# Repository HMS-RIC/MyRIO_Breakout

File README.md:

# MyRIO_Breakout
Breakout board for NI MyRIO. Brings to BNC connectors 4 analog out, 4 analog in and 14 digital IO. Includes 2 channels of lick detection, 2 solenoid drivers and 3 LED drivers

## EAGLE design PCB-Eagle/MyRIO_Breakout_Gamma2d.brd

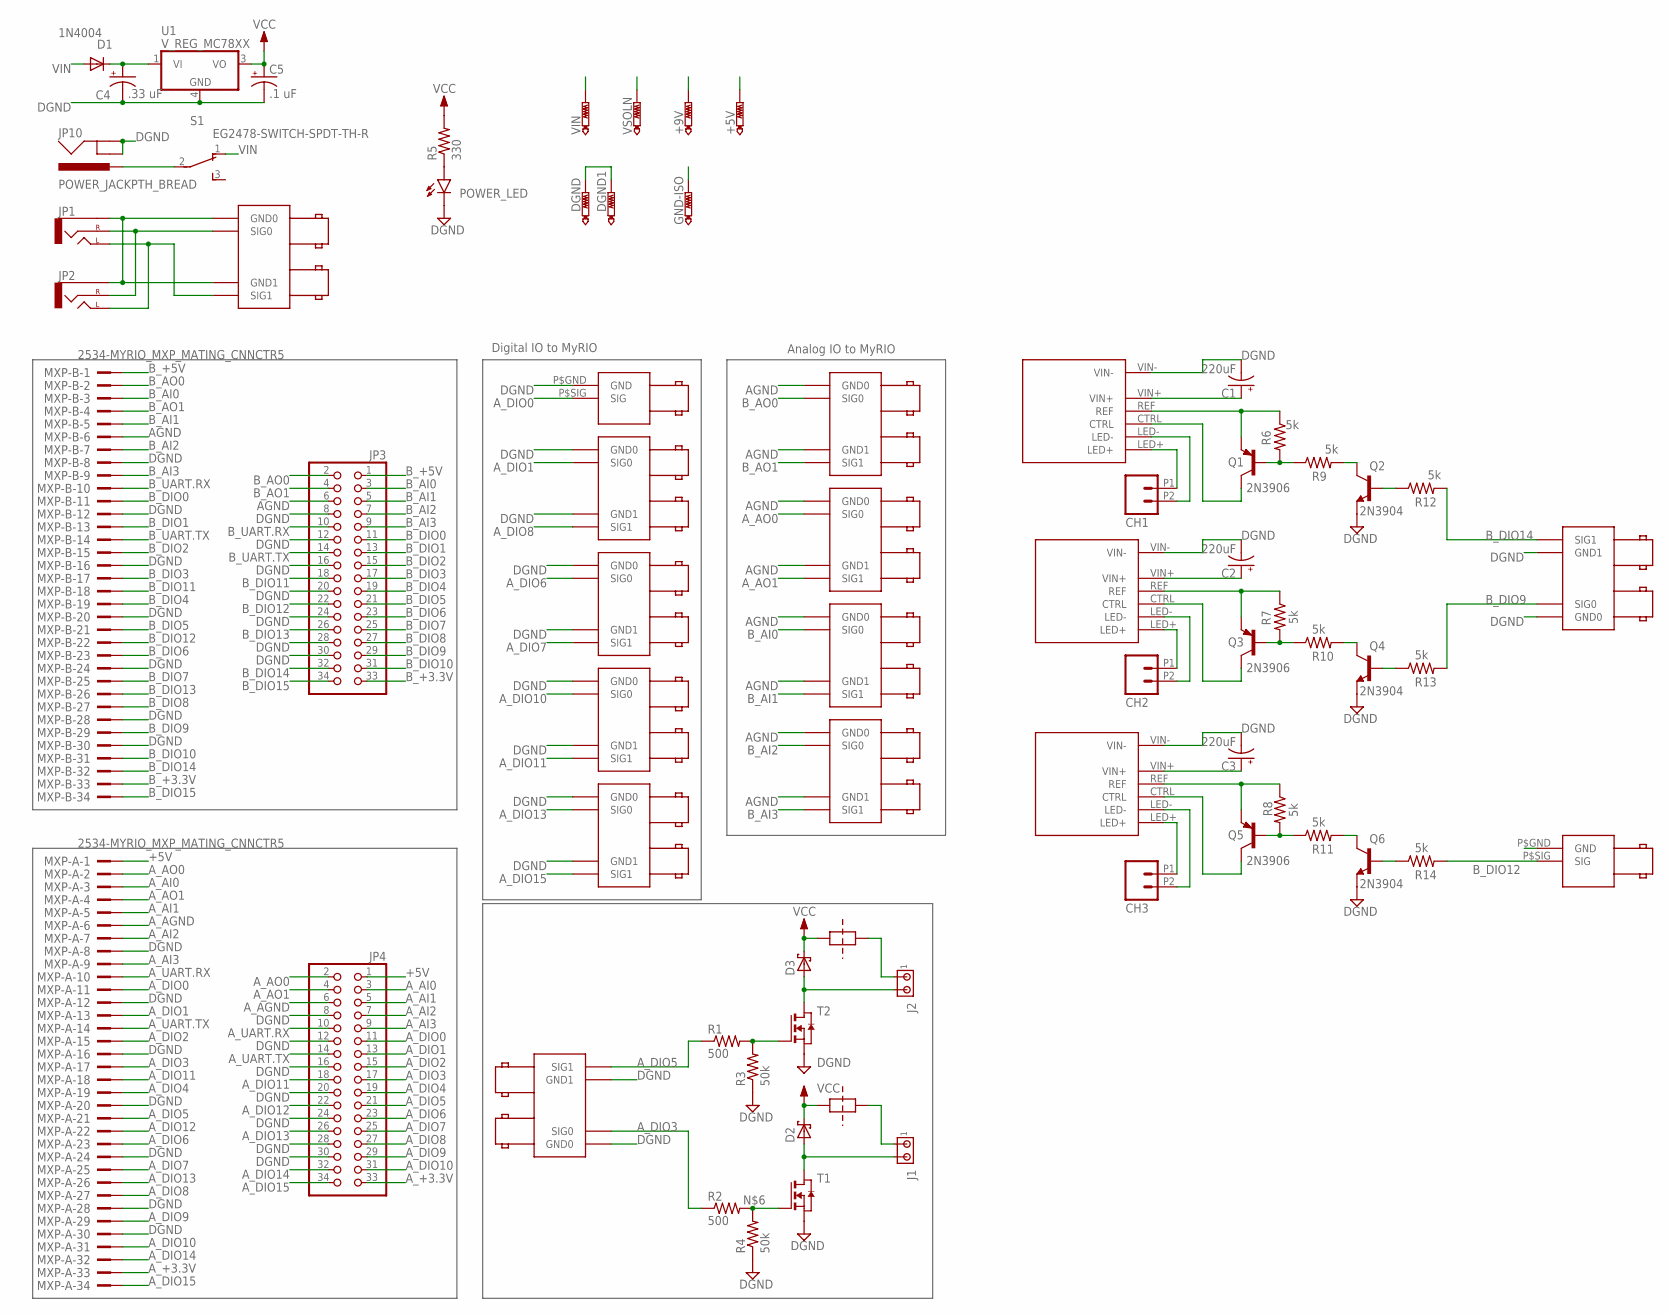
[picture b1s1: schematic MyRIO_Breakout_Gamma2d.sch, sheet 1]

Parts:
+5V, +9V: PTR1PAD1-13Y; P1-13Y
AAO_0,1: BNC_RIGHT_ANGLE_DOUBLE
ACTV_REC: BNC_RIGHT_ANGLE
AUDIO: BNC_RIGHT_ANGLE_DOUBLE
BAI_0,1, BAI_2,3: BNC_RIGHT_ANGLE_DOUBLE
BAO_0,1: BNC_RIGHT_ANGLE_DOUBLE
BUCKPUCK1, BUCKPUCK2, BUCKPUCK3: BUCKPUCK-350-I; BUCKPUCK_I
C1, C2, C3: 220uF; E5-10,5
C4: .33 uF; E2,5-5
C5: .1 uF; E2,5-5
CAMERA: BNC_RIGHT_ANGLE_DOUBLE
CH1, CH2, CH3: M022.54MM_SCREWTERM; 1X02_2.54_SCREWTERM
D1: 1N4004; DO41-10
D2, D3: SCHOTTKY-DIODE; DIODE_SMB
DGND, DGND1: PTR1PAD1-13Y; P1-13Y
D_FREE1_2, D_FREE3_4: BNC_RIGHT_ANGLE_DOUBLE
GND-ISO: PTR1PAD1-13Y; P1-13Y
J1, J2: MTA02-100; 10X02MTA
JP1, JP2: AUDIO-JACKPTH; AUDIO-JACK
JP3, JP4: PINHD-2X17; 2X17
JP5, JP6: CUTABLE_RESISTOR_JUMPER1206; 1206_WITH_TRACE
JP10: POWER_JACKPTH_BREAD; POWER_JACK_PTH_BREAD
LED_CUE_3: BNC_RIGHT_ANGLE
LED_MASK_1,2: BNC_RIGHT_ANGLE_DOUBLE
MXP-A: 2534-MYRIO_MXP_MATING_CNNCTR5; PAK100/2500-5-34-MXP_CONNCTR
MXP-B: 2534-MYRIO_MXP_MATING_CNNCTR5; PAK100/2500-5-34-MXP_CONNCTR
POWER_LED: LED3MM
Q1, Q3, Q5: 2N3906; SOT23-BEC
Q2, Q4, Q6: 2N3904; SOT23-BEC
R1, R2: 500; M1206
R3, R4: 50k; M1206
R5: 330; 0207/10
R6, R7, R8, R9, R10, R11, R12, R13, R14: 5k; 0805S
S1: EG2478-SWITCH-SPDT-TH-R; ESWITCH_500-SSP1M6
SHUTTER: BNC_RIGHT_ANGLE_DOUBLE
SLN: BNC_RIGHT_ANGLE_DOUBLE
T1, T2: NMOSSOT223; SOT223
U1: V_REG_MC78XX; DPAK
VIN: PTR1PAD1-13Y; P1-13Y
VSOLN: PTR1PAD1-13Y; P1-13Y

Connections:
+5V: +5V.TP, JP4.1, MXP-A.1; also elsewhere on the board
+9V: +9V.TP; also elsewhere on the board
AGND: AAO_0,1.P$GND0 (GND0), AAO_0,1.P$GND1 (GND1), BAI_0,1.P$GND0 (GND0), BAI_0,1.P$GND1 (GND1), BAI_2,3.P$GND0 (GND0), BAI_2,3.P$GND1 (GND1), BAO_0,1.P$GND0 (GND0), BAO_0,1.P$GND1 (GND1), JP3.6, MXP-B.6; also elsewhere on the board
A_+3.3V: JP4.33, MXP-A.33
A_AGND: JP4.6, MXP-A.6
A_AI0: JP4.3, MXP-A.3
A_AI1: JP4.5, MXP-A.5
A_AI2: JP4.7, MXP-A.7
A_AI3: JP4.9, MXP-A.9
A_AO0: AAO_0,1.P$SIG0 (SIG0), JP4.2, MXP-A.2
A_AO1: AAO_0,1.P$SIG1 (SIG1), JP4.4, MXP-A.4
A_DIO0: ACTV_REC.P$SIG (SIG), JP4.11, MXP-A.11
A_DIO1: CAMERA.P$SIG0 (SIG0), JP4.13, MXP-A.13
A_DIO2: JP4.15, MXP-A.15; also elsewhere on the board
A_DIO3: JP4.17, MXP-A.17, R2.1, SLN.P$SIG0 (SIG0)
A_DIO4: JP4.19, MXP-A.19; also elsewhere on the board
A_DIO5: JP4.21, MXP-A.21, R1.1, SLN.P$SIG1 (SIG1)
A_DIO6: JP4.23, MXP-A.23, SHUTTER.P$SIG0 (SIG0)
A_DIO7: JP4.25, MXP-A.25, SHUTTER.P$SIG1 (SIG1)
A_DIO8: CAMERA.P$SIG1 (SIG1), JP4.27, MXP-A.27
A_DIO9: JP4.29, MXP-A.29
A_DIO10: D_FREE1_2.P$SIG0 (SIG0), JP4.31, MXP-A.31
A_DIO11: D_FREE1_2.P$SIG1 (SIG1), JP4.18, MXP-A.18
A_DIO12: JP4.22, MXP-A.22
A_DIO13: D_FREE3_4.P$SIG0 (SIG0), JP4.26, MXP-A.26
A_DIO14: JP4.32, MXP-A.32
A_DIO15: D_FREE3_4.P$SIG1 (SIG1), JP4.34, MXP-A.34
A_UART.RX: JP4.10, MXP-A.10
A_UART.TX: JP4.14, MXP-A.14
BCKPCK_CTRL2: Q4.C, R10.2
BCKPCK_CTRL3: Q6.C, R11.2
B_+3.3V: JP3.33, MXP-B.33
B_+5V: JP3.1, MXP-B.1
B_AI0: BAI_0,1.P$SIG0 (SIG0), JP3.3, MXP-B.3
B_AI1: BAI_0,1.P$SIG1 (SIG1), JP3.5, MXP-B.5
B_AI2: BAI_2,3.P$SIG0 (SIG0), JP3.7, MXP-B.7
B_AI3: BAI_2,3.P$SIG1 (SIG1), JP3.9, MXP-B.9
B_AO0: BAO_0,1.P$SIG0 (SIG0), JP3.2, MXP-B.2
B_AO1: BAO_0,1.P$SIG1 (SIG1), JP3.4, MXP-B.4
B_DIO0: JP3.11, MXP-B.11
B_DIO1: JP3.13, MXP-B.13
B_DIO2: JP3.15, MXP-B.15
B_DIO3: JP3.17, MXP-B.17
B_DIO4: JP3.19, MXP-B.19
B_DIO5: JP3.21, MXP-B.21
B_DIO6: JP3.23, MXP-B.23
B_DIO7: JP3.25, MXP-B.25
B_DIO8: JP3.27, MXP-B.27
B_DIO9: JP3.29, LED_MASK_1,2.P$SIG0 (SIG0), MXP-B.29, R13.2
B_DIO10: JP3.31, MXP-B.31
B_DIO11: JP3.18, MXP-B.18
B_DIO12: JP3.22, LED_CUE_3.P$SIG (SIG), MXP-B.22, R14.2
B_DIO13: JP3.26, MXP-B.26
B_DIO14: JP3.32, LED_MASK_1,2.P$SIG1 (SIG1), MXP-B.32, R12.2
B_DIO15: JP3.34, MXP-B.34
B_UART.RX: JP3.10, MXP-B.10
B_UART.TX: JP3.14, MXP-B.14
CTRL1: BUCKPUCK1.CTRL, Q1.C
CTRL2: BUCKPUCK2.CTRL, Q3.C
CTRL3: BUCKPUCK3.CTRL, Q5.C
DGND: ACTV_REC.P$GND (GND), BUCKPUCK1.LED-, BUCKPUCK1.VIN-, BUCKPUCK2.LED-, BUCKPUCK2.VIN-, BUCKPUCK3.LED-, BUCKPUCK3.VIN-, C1.-, C2.-, C3.-, C4.-, C5.-, CAMERA.P$GND0 (GND0), CAMERA.P$GND1 (GND1), CH1.P2 (2), CH2.P2 (2), CH3.P2 (2), DGND.TP, DGND1.TP, D_FREE1_2.P$GND0 (GND0), D_FREE1_2.P$GND1 (GND1), D_FREE3_4.P$GND0 (GND0), D_FREE3_4.P$GND1 (GND1), JP3.8, JP3.12, JP3.16, JP3.20, JP3.24, JP3.28, JP3.30, JP4.8, JP4.12, JP4.16, JP4.20, JP4.24, JP4.28, JP4.30, JP10.GND, JP10.GNDBREAK, LED_CUE_3.P$GND (GND), LED_MASK_1,2.P$GND0 (GND0), LED_MASK_1,2.P$GND1 (GND1), MXP-A.8, MXP-A.12, MXP-A.16, MXP-A.20, MXP-A.24, MXP-A.28, MXP-A.30, MXP-B.8, MXP-B.12, MXP-B.16, MXP-B.20, MXP-B.24, MXP-B.28, MXP-B.30, POWER_LED.K (C), Q2.E, Q4.E, Q6.E, R3.1, R4.1, SHUTTER.P$GND0 (GND0), SHUTTER.P$GND1 (GND1), SLN.P$GND0 (GND0), SLN.P$GND1 (GND1), T1.3 (S), T2.3 (S), U1.4 (GND); also elsewhere on the board
GND-ISO: GND-ISO.TP; also elsewhere on the board
LED1+: BUCKPUCK1.LED+, CH1.P1 (1)
LED2+: BUCKPUCK2.LED+, CH2.P1 (1)
LED3+: BUCKPUCK3.LED+, CH3.P1 (1)
unnamed: R1.2, R3.2, T2.1 (G)
unnamed: AUDIO.P$GND0 (GND0), AUDIO.P$GND1 (GND1), JP1.SLEEVE, JP2.SLEEVE
unnamed: AUDIO.P$SIG0 (SIG0), JP1.RING (RIGHT), JP2.RING (RIGHT)
unnamed: AUDIO.P$SIG1 (SIG1), JP1.TIP (LEFT), JP2.TIP (LEFT)
unnamed: R2.2, R4.2, T1.1 (G)
unnamed: BUCKPUCK3.REF, Q5.E, R8.1
unnamed: POWER_LED.A, R5.1
unnamed: Q5.B, R8.2, R11.1
unnamed: BUCKPUCK1.VIN+, BUCKPUCK2.VIN+, BUCKPUCK3.VIN+, C1.+, C2.+, C3.+, C4.+, D1.C, U1.1 (VI), VIN.TP
unnamed: BUCKPUCK1.REF, Q1.E, R6.1
unnamed: BUCKPUCK2.REF, Q3.E, R7.1
unnamed: Q6.B, R14.1
unnamed: Q4.B, R13.1
unnamed: Q1.B, R6.2, R9.1
unnamed: Q2.B, R12.1
unnamed: J1.1, JP6.2
unnamed: Q3.B, R7.2, R10.1
unnamed: JP10.PWR, S1.2
unnamed: J2.1, JP5.2
unnamed: Q2.C, R9.2
VCC: C5.+, D2.C (A), D3.C (A), JP5.1, JP6.1, R5.2, U1.3 (VO), VSOLN.TP
VIN: D1.A, S1.1
VOUT-1: D2.A (C), J1.2, T1.2 (D), T1.4 (D)
VOUT-2: D3.A (C), J2.2, T2.2 (D), T2.4 (D)

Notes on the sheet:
Digital IO to MyRIO
Analog IO to MyRIO

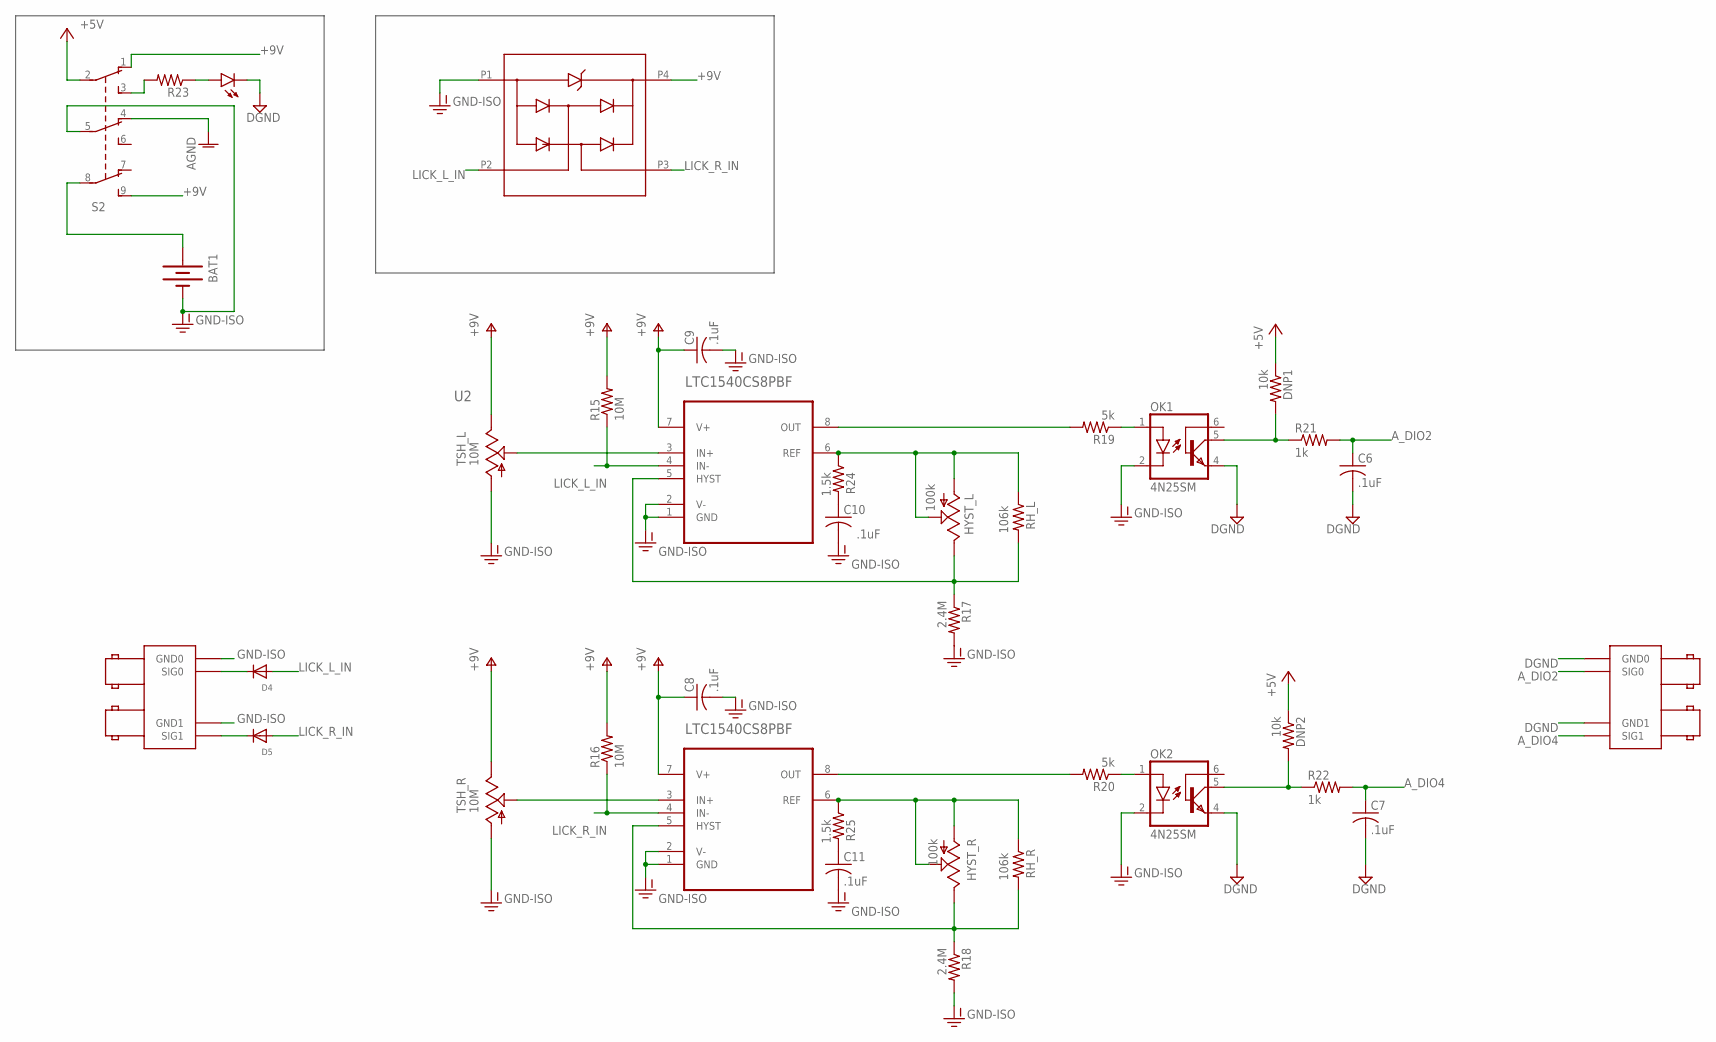
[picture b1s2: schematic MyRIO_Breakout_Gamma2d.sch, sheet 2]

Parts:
BAT1: BATTERY9V; BATTCON_9V
C6, C7, C8, C9, C10, C11: .1uF; C0805
D4, D5: DIODE_SOD-123FL; SOD-123FL
DNP1, DNP2: 10k; M0805
HYST_L: 100k; B25P
HYST_R: 100k; B25P
ISOLATED: LED3MM
LICK: BNC_RIGHT_ANGLE_DOUBLE
LICK_INPUTS: BNC_RIGHT_ANGLE_DOUBLE
OK1, OK2: 4N25SM; DIL6-SMD
R15, R16: 10M; M0805
R17, R18: 2.4M; M0805
R19, R20: 5k; M0805
R21, R22: 1k; M0805
R23: 330; 0207/10
R24, R25: 1.5k; M0805
RH_L: 106k; M0805
RH_R: 106k; M0805
S2: SWITCH-3PDT-TH-V; NKK-M20-9PIN-VERTICAL
TSH_L: 10M; B25P
TSH_R: 10M; B25P
U2, U3: LTC1540CS8PBF; SOIC127P600X175-8N
U$1: CD143A-12_TVS; SOT-143

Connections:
+5V: DNP1.1, DNP2.1, S2.2 (P1); also elsewhere on the board
+9V: C8.1, C9.1, R15.2, R16.2, S2.1 (O1), S2.9 (S3), TSH_L.E, TSH_R.E, U2.7 (V+), U3.7 (V+), U$1.P4; also elsewhere on the board
AGND: S2.4 (O2); also elsewhere on the board
A_DIO2: C6.1, LICK.P$SIG0 (SIG0), R21.2; also elsewhere on the board
A_DIO4: C7.1, LICK.P$SIG1 (SIG1), R22.2; also elsewhere on the board
DGND: C6.2, C7.2, ISOLATED.K (C), LICK.P$GND0 (GND0), LICK.P$GND1 (GND1), OK1.4 (EMI), OK2.4 (EMI); also elsewhere on the board
GND-ISO: BAT1.-, C8.2, C9.2, C10.2, C11.2, LICK_INPUTS.P$GND0 (GND0), LICK_INPUTS.P$GND1 (GND1), OK1.2 (C), OK2.2 (C), R17.2, R18.2, S2.5 (P2), TSH_L.A, TSH_R.A, U2.1 (GND), U2.2 (V-), U3.1 (GND), U3.2 (V-), U$1.P1; also elsewhere on the board
LICK_L_IN: D4.A, R15.1, U2.4 (IN-), U$1.P2
LICK_R_IN: D5.A, R16.1, U3.4 (IN-), U$1.P3
unnamed: D4.C, LICK_INPUTS.P$SIG0 (SIG0)
unnamed: C10.1, R24.2
unnamed: D5.C, LICK_INPUTS.P$SIG1 (SIG1)
unnamed: C11.1, R25.2
unnamed: BAT1.+, S2.8 (P3)
unnamed: ISOLATED.A, R23.1
unnamed: TSH_R.S, U3.3 (IN+)
unnamed: R23.2, S2.3 (S1)
unnamed: OK1.1 (A), R19.1
unnamed: R19.2, U2.8 (OUT)
unnamed: DNP1.2, OK1.5 (COL), R21.1
unnamed: HYST_L.A, HYST_L.S, R24.1, RH_L.1, U2.6 (REF)
unnamed: HYST_L.E, R17.1, RH_L.2, U2.5 (HYST)
unnamed: OK2.1 (A), R20.1
unnamed: R20.2, U3.8 (OUT)
unnamed: TSH_L.S, U2.3 (IN+)
unnamed: DNP2.2, OK2.5 (COL), R22.1
unnamed: HYST_R.A, HYST_R.S, R25.1, RH_R.1, U3.6 (REF)
unnamed: HYST_R.E, R18.1, RH_R.2, U3.5 (HYST)

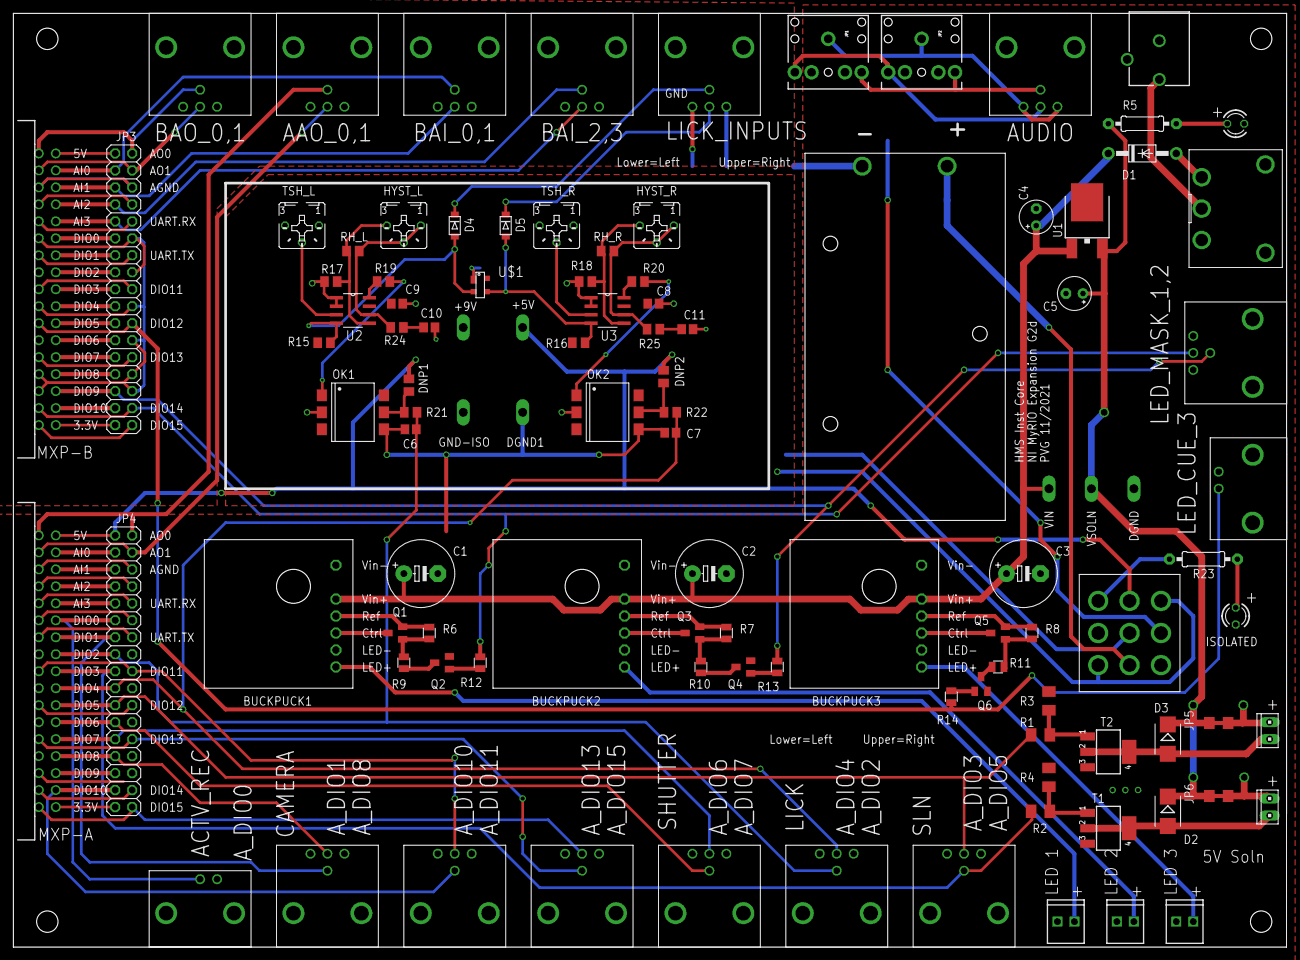
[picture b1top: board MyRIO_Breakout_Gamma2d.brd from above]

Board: 2 copper layers, 190.5 x 139.7 mm, 107 parts (0 on the bottom side), 110 nets.

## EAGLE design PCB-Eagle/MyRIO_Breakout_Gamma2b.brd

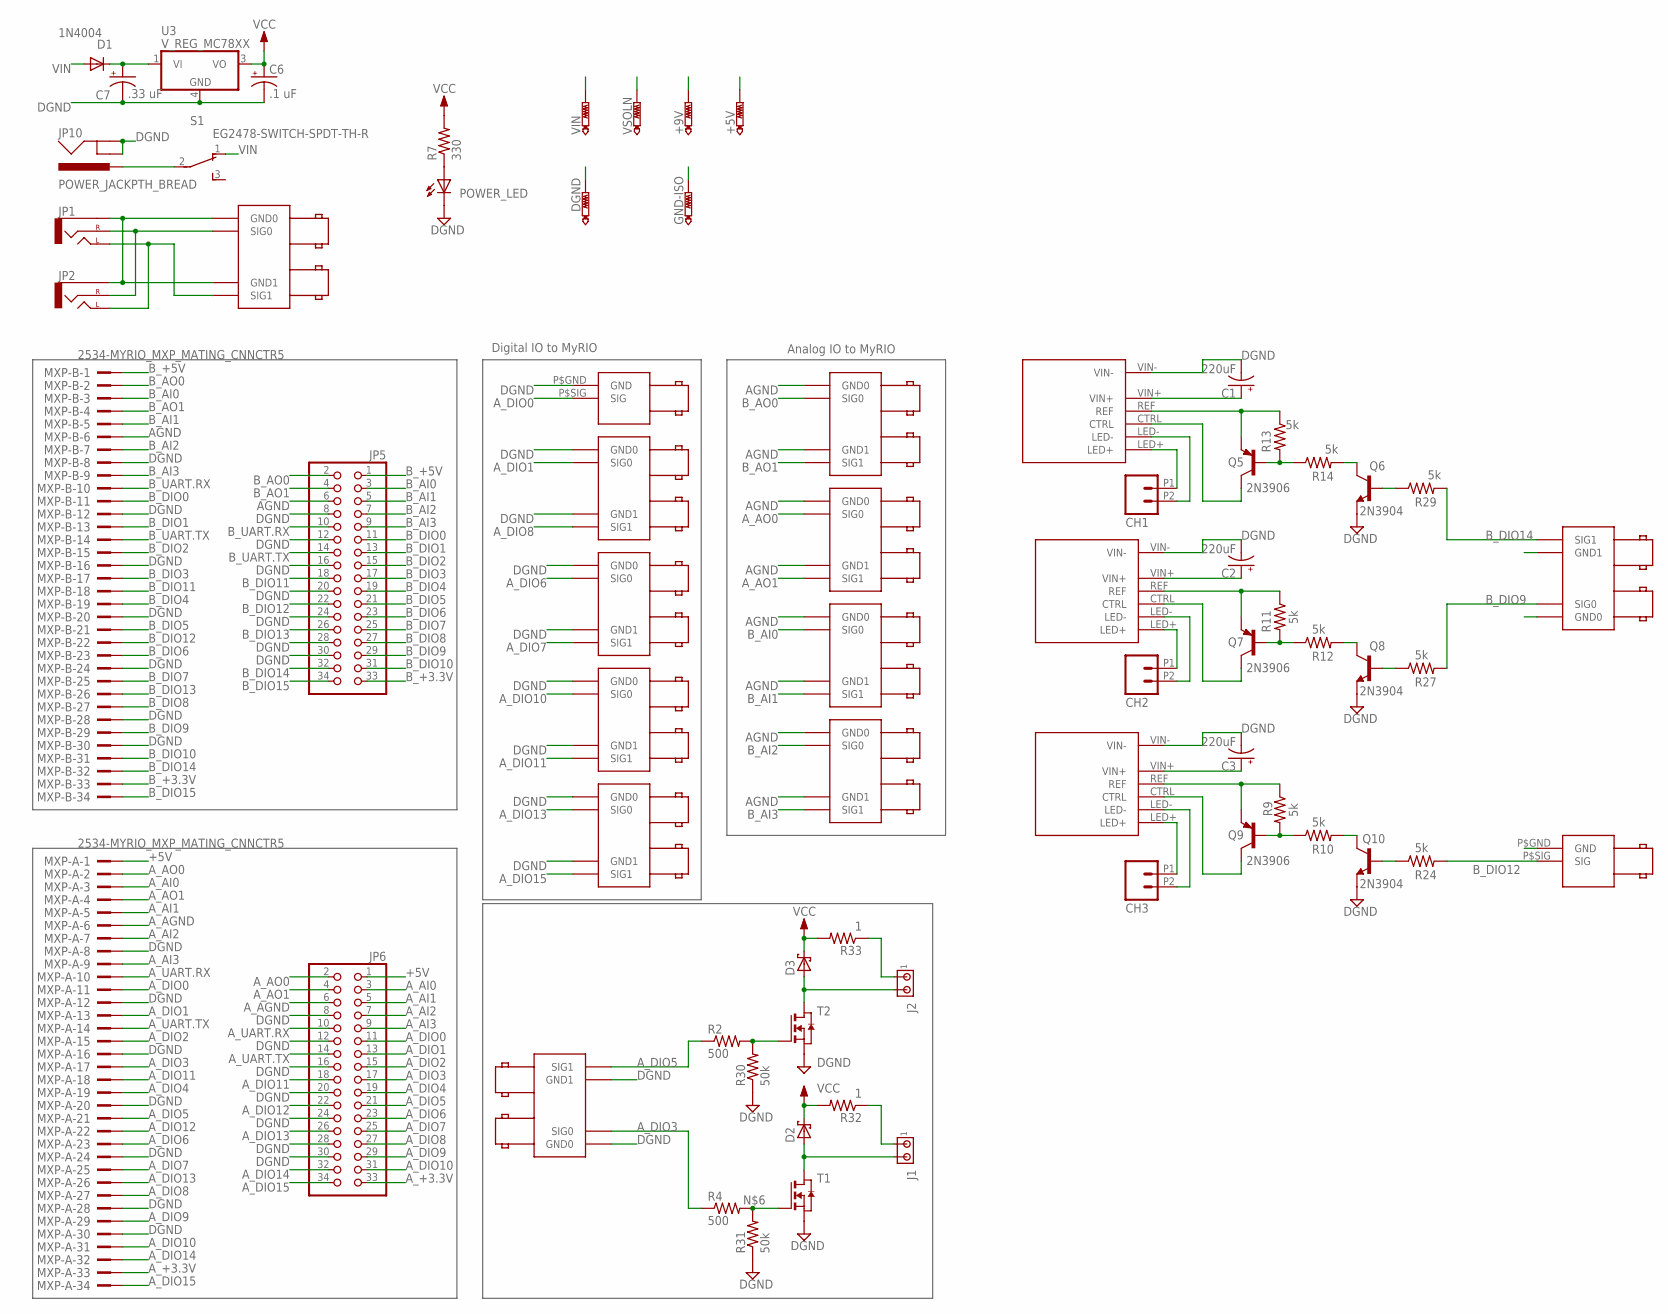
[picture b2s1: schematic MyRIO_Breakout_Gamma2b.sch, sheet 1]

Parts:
+5V, +9V: PTR1PAD1-17Y; P1-17Y
AAO_0,1: BNC_RIGHT_ANGLE_DOUBLE
ACTV_REC: BNC_RIGHT_ANGLE
AUDIO: BNC_RIGHT_ANGLE_DOUBLE
BAI_0,1, BAI_2,3: BNC_RIGHT_ANGLE_DOUBLE
BAO_0,1: BNC_RIGHT_ANGLE_DOUBLE
BUCKPUCK1, BUCKPUCK2, BUCKPUCK3: BUCKPUCK-350-I; BUCKPUCK_I
C1, C2, C3: 220uF; E5-10,5
C6: .1 uF; E2,5-5
C7: .33 uF; E2,5-5
CAMERA: BNC_RIGHT_ANGLE_DOUBLE
CH1, CH2, CH3: M022.54MM_SCREWTERM; 1X02_2.54_SCREWTERM
D1: 1N4004; DO41-10
D2, D3: SCHOTTKY-DIODE; DIODE_SMB
DGND: PTR1PAD1-17Y; P1-17Y
D_FREE1_2, D_FREE3_4: BNC_RIGHT_ANGLE_DOUBLE
GND-ISO: PTR1PAD1-17Y; P1-17Y
J1, J2: MTA02-100; 10X02MTA
JP1, JP2: AUDIO-JACKPTH; AUDIO-JACK
JP5, JP6: PINHD-2X17; 2X17
JP10: POWER_JACKPTH_BREAD; POWER_JACK_PTH_BREAD
LED_CUE: BNC_RIGHT_ANGLE
LED_MASK: BNC_RIGHT_ANGLE_DOUBLE
MXP-A: 2534-MYRIO_MXP_MATING_CNNCTR5; PAK100/2500-5-34-MXP_CONNCTR
MXP-B: 2534-MYRIO_MXP_MATING_CNNCTR5; PAK100/2500-5-34-MXP_CONNCTR
POWER_LED: LED3MM
Q5, Q7, Q9: 2N3906; SOT23-BEC
Q6, Q8, Q10: 2N3904; SOT23-BEC
R2, R4: 500; M1206
R7: 330; 0207/10
R9, R10, R11, R12, R13, R14, R24, R27, R29: 5k; 0805S
R30, R31: 50k; M1206
R32, R33: 1; M1206
S1: EG2478-SWITCH-SPDT-TH-R; ESWITCH_500-SSP1M6
SHUTTER: BNC_RIGHT_ANGLE_DOUBLE
SLN: BNC_RIGHT_ANGLE_DOUBLE
T1, T2: NMOSSOT223; SOT223
U3: V_REG_MC78XX; DPAK
VIN: PTR1PAD1-17Y; P1-17Y
VSOLN: PTR1PAD1-17Y; P1-17Y

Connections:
+5V: +5V.TP, JP6.1, MXP-A.1; also elsewhere on the board
+9V: +9V.TP; also elsewhere on the board
AGND: AAO_0,1.P$GND0 (GND0), AAO_0,1.P$GND1 (GND1), BAI_0,1.P$GND0 (GND0), BAI_0,1.P$GND1 (GND1), BAI_2,3.P$GND0 (GND0), BAI_2,3.P$GND1 (GND1), BAO_0,1.P$GND0 (GND0), BAO_0,1.P$GND1 (GND1), JP5.6, MXP-B.6; also elsewhere on the board
A_+3.3V: JP6.33, MXP-A.33
A_AGND: JP6.6, MXP-A.6
A_AI0: JP6.3, MXP-A.3
A_AI1: JP6.5, MXP-A.5
A_AI2: JP6.7, MXP-A.7
A_AI3: JP6.9, MXP-A.9
A_AO0: AAO_0,1.P$SIG0 (SIG0), JP6.2, MXP-A.2
A_AO1: AAO_0,1.P$SIG1 (SIG1), JP6.4, MXP-A.4
A_DIO0: ACTV_REC.P$SIG (SIG), JP6.11, MXP-A.11
A_DIO1: CAMERA.P$SIG0 (SIG0), JP6.13, MXP-A.13
A_DIO2: JP6.15, MXP-A.15; also elsewhere on the board
A_DIO3: JP6.17, MXP-A.17, R4.1, SLN.P$SIG0 (SIG0)
A_DIO4: JP6.19, MXP-A.19; also elsewhere on the board
A_DIO5: JP6.21, MXP-A.21, R2.1, SLN.P$SIG1 (SIG1)
A_DIO6: JP6.23, MXP-A.23, SHUTTER.P$SIG0 (SIG0)
A_DIO7: JP6.25, MXP-A.25, SHUTTER.P$SIG1 (SIG1)
A_DIO8: CAMERA.P$SIG1 (SIG1), JP6.27, MXP-A.27
A_DIO9: JP6.29, MXP-A.29
A_DIO10: D_FREE1_2.P$SIG0 (SIG0), JP6.31, MXP-A.31
A_DIO11: D_FREE1_2.P$SIG1 (SIG1), JP6.18, MXP-A.18
A_DIO12: JP6.22, MXP-A.22
A_DIO13: D_FREE3_4.P$SIG0 (SIG0), JP6.26, MXP-A.26
A_DIO14: JP6.32, MXP-A.32
A_DIO15: D_FREE3_4.P$SIG1 (SIG1), JP6.34, MXP-A.34
A_UART.RX: JP6.10, MXP-A.10
A_UART.TX: JP6.14, MXP-A.14
BCKPCK_CTRL2: Q8.C, R12.2
BCKPCK_CTRL3: Q10.C, R10.2
B_+3.3V: JP5.33, MXP-B.33
B_+5V: JP5.1, MXP-B.1
B_AI0: BAI_0,1.P$SIG0 (SIG0), JP5.3, MXP-B.3
B_AI1: BAI_0,1.P$SIG1 (SIG1), JP5.5, MXP-B.5
B_AI2: BAI_2,3.P$SIG0 (SIG0), JP5.7, MXP-B.7
B_AI3: BAI_2,3.P$SIG1 (SIG1), JP5.9, MXP-B.9
B_AO0: BAO_0,1.P$SIG0 (SIG0), JP5.2, MXP-B.2
B_AO1: BAO_0,1.P$SIG1 (SIG1), JP5.4, MXP-B.4
B_DIO0: JP5.11, MXP-B.11
B_DIO1: JP5.13, MXP-B.13
B_DIO2: JP5.15, MXP-B.15
B_DIO3: JP5.17, MXP-B.17
B_DIO4: JP5.19, MXP-B.19
B_DIO5: JP5.21, MXP-B.21
B_DIO6: JP5.23, MXP-B.23
B_DIO7: JP5.25, MXP-B.25
B_DIO8: JP5.27, MXP-B.27
B_DIO9: JP5.29, LED_MASK.P$SIG0 (SIG0), MXP-B.29, R27.2
B_DIO10: JP5.31, MXP-B.31
B_DIO11: JP5.18, MXP-B.18
B_DIO12: JP5.22, LED_CUE.P$SIG (SIG), MXP-B.22, R24.2
B_DIO13: JP5.26, MXP-B.26
B_DIO14: JP5.32, LED_MASK.P$SIG1 (SIG1), MXP-B.32, R29.2
B_DIO15: JP5.34, MXP-B.34
B_UART.RX: JP5.10, MXP-B.10
B_UART.TX: JP5.14, MXP-B.14
CTRL1: BUCKPUCK1.CTRL, Q5.C
CTRL2: BUCKPUCK2.CTRL, Q7.C
CTRL3: BUCKPUCK3.CTRL, Q9.C
DGND: ACTV_REC.P$GND (GND), BUCKPUCK1.LED-, BUCKPUCK1.VIN-, BUCKPUCK2.LED-, BUCKPUCK2.VIN-, BUCKPUCK3.LED-, BUCKPUCK3.VIN-, C1.-, C2.-, C3.-, C6.-, C7.-, CAMERA.P$GND0 (GND0), CAMERA.P$GND1 (GND1), CH1.P2 (2), CH2.P2 (2), CH3.P2 (2), DGND.TP, D_FREE1_2.P$GND0 (GND0), D_FREE1_2.P$GND1 (GND1), D_FREE3_4.P$GND0 (GND0), D_FREE3_4.P$GND1 (GND1), JP5.8, JP5.12, JP5.16, JP5.20, JP5.24, JP5.28, JP5.30, JP6.8, JP6.12, JP6.16, JP6.20, JP6.24, JP6.28, JP6.30, JP10.GND, JP10.GNDBREAK, LED_CUE.P$GND (GND), LED_MASK.P$GND0 (GND0), LED_MASK.P$GND1 (GND1), MXP-A.8, MXP-A.12, MXP-A.16, MXP-A.20, MXP-A.24, MXP-A.28, MXP-A.30, MXP-B.8, MXP-B.12, MXP-B.16, MXP-B.20, MXP-B.24, MXP-B.28, MXP-B.30, POWER_LED.K (C), Q6.E, Q8.E, Q10.E, R30.1, R31.1, SHUTTER.P$GND0 (GND0), SHUTTER.P$GND1 (GND1), SLN.P$GND0 (GND0), SLN.P$GND1 (GND1), T1.3 (S), T2.3 (S), U3.4 (GND); also elsewhere on the board
GND-ISO: GND-ISO.TP; also elsewhere on the board
LED1+: BUCKPUCK1.LED+, CH1.P1 (1)
LED2+: BUCKPUCK2.LED+, CH2.P1 (1)
LED3+: BUCKPUCK3.LED+, CH3.P1 (1)
unnamed: R2.2, R30.2, T2.1 (G)
unnamed: AUDIO.P$GND0 (GND0), AUDIO.P$GND1 (GND1), JP1.SLEEVE, JP2.SLEEVE
unnamed: AUDIO.P$SIG0 (SIG0), JP1.RING (RIGHT), JP2.RING (RIGHT)
unnamed: AUDIO.P$SIG1 (SIG1), JP1.TIP (LEFT), JP2.TIP (LEFT)
unnamed: R4.2, R31.2, T1.1 (G)
unnamed: BUCKPUCK3.REF, Q9.E, R9.1
unnamed: POWER_LED.A, R7.1
unnamed: Q9.B, R9.2, R10.1
unnamed: BUCKPUCK1.VIN+, BUCKPUCK2.VIN+, BUCKPUCK3.VIN+, C1.+, C2.+, C3.+, C7.+, D1.C, U3.1 (VI), VIN.TP
unnamed: BUCKPUCK1.REF, Q5.E, R13.1
unnamed: BUCKPUCK2.REF, Q7.E, R11.1
unnamed: Q10.B, R24.1
unnamed: Q8.B, R27.1
unnamed: Q5.B, R13.2, R14.1
unnamed: Q6.B, R29.1
unnamed: J1.1, R32.1
unnamed: Q7.B, R11.2, R12.1
unnamed: JP10.PWR, S1.2
unnamed: J2.1, R33.1
unnamed: Q6.C, R14.2
VCC: C6.+, D2.C (A), D3.C (A), R7.2, R32.2, R33.2, U3.3 (VO), VSOLN.TP
VIN: D1.A, S1.1
VOUT-1: D2.A (C), J1.2, T1.2 (D), T1.4 (D)
VOUT-2: D3.A (C), J2.2, T2.2 (D), T2.4 (D)

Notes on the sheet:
Digital IO to MyRIO
Analog IO to MyRIO

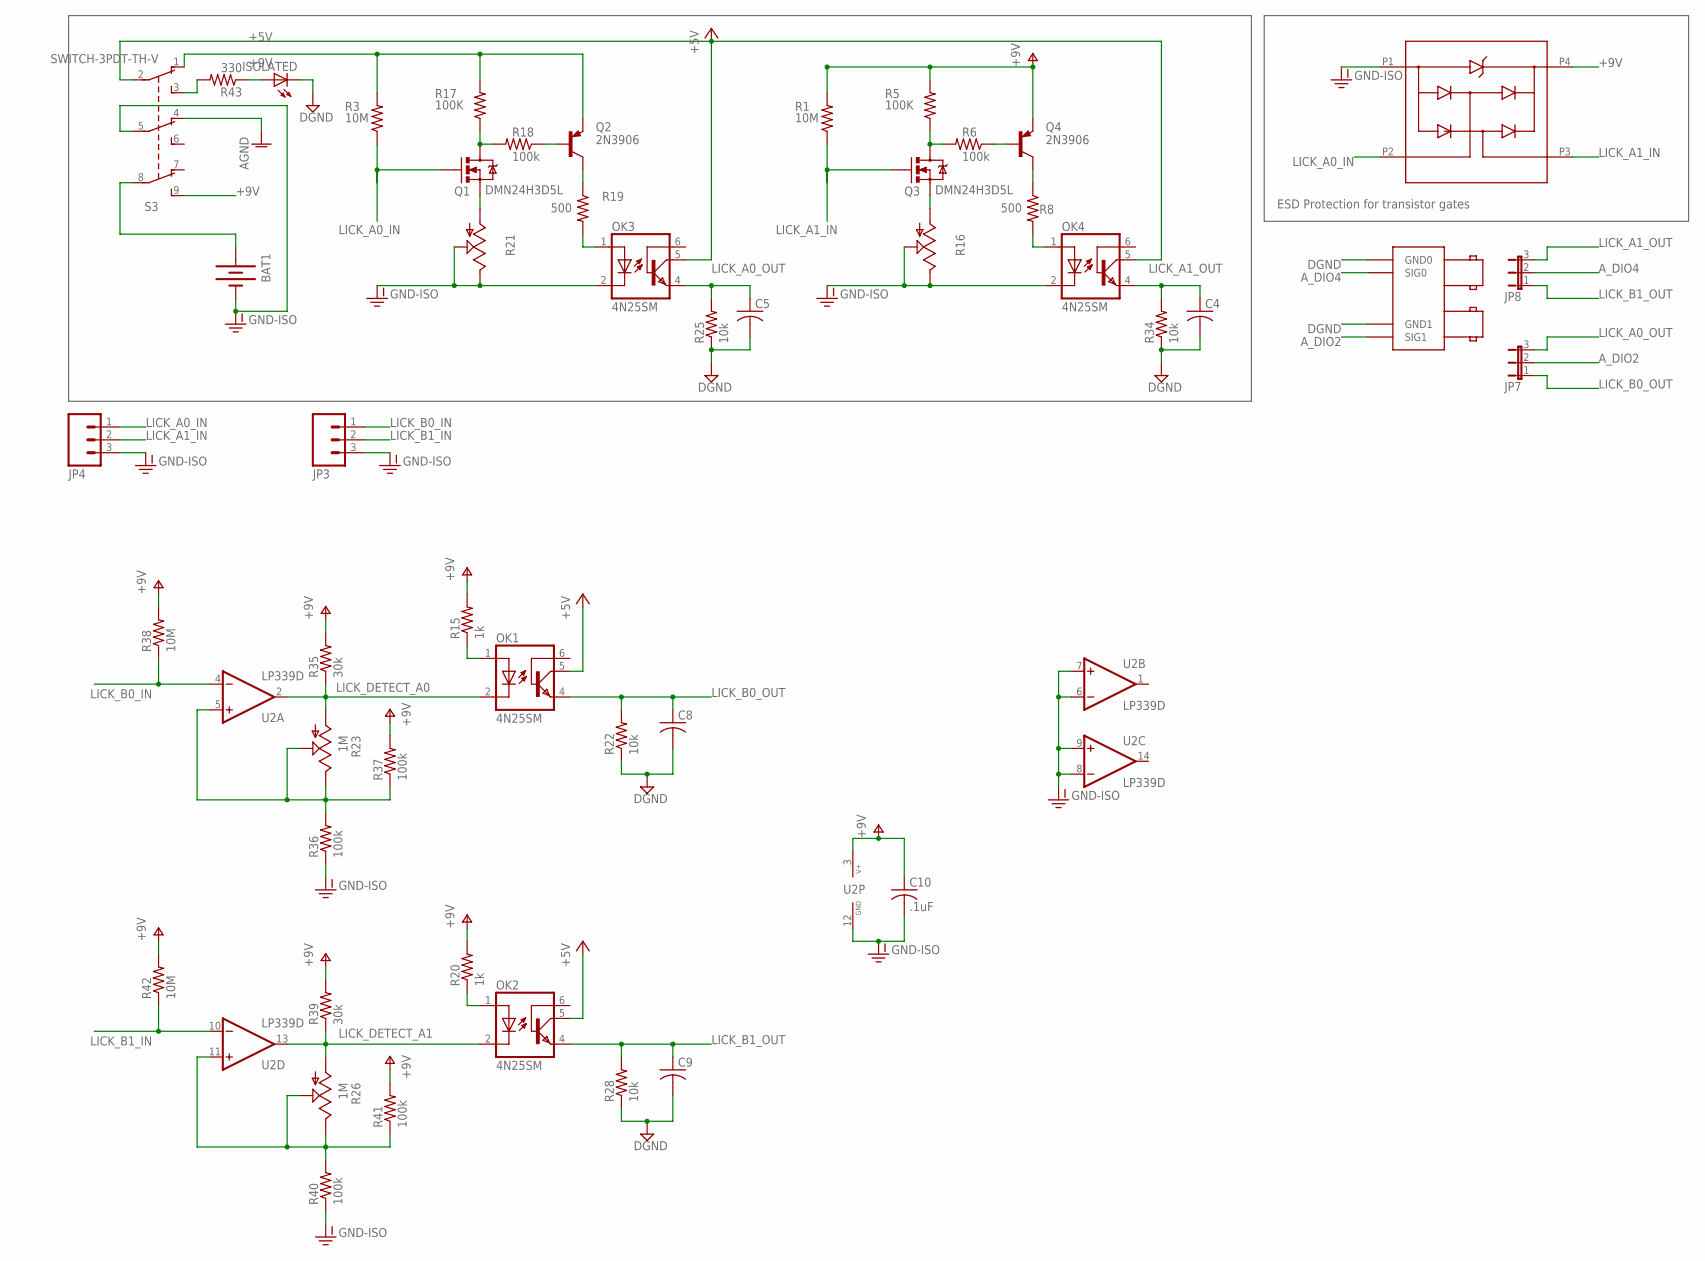
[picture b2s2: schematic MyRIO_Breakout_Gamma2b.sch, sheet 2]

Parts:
BAT1: BATTERY9V; BATTCON_9V
C4, C5, C8, C9: C-US025-024X044; C025-024X044
C10: .1uF; C0805K
ISOLATED: LED3MM
JP3, JP4: M03POLAR; MOLEX-1X3
JP7, JP8: JP2E; JP2
LICK: BNC_RIGHT_ANGLE_DOUBLE
OK1, OK2, OK3, OK4: 4N25SM; DIL6-SMD
Q1, Q3: DMN24H3D5L; SOT23-3
Q2, Q4: 2N3906; SOT23-BEC
R1, R3: 10M; 0805S
R5, R17: 100K; 0805S
R6, R18: 100k; 0805S
R8, R19: 500; 0805S
R15, R20: 1k; M0805
R16, R21: TRIM_US-B25P; B25P
R22, R25, R28, R34: 10k; 0204V
R23, R26: 1M; B25P
R35, R39: 30k; M0805
R36, R37, R40, R41: 100k; M0805
R38, R42: 10M; M0805
R43: 330; 0207/10
S3: SWITCH-3PDT-TH-V; NKK-M20-9PIN-VERTICAL
U1: CD143A-12_TVS; SOT-143
U2: LP339D; SO14

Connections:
+5V: OK1.5 (COL), OK2.5 (COL), OK3.5 (COL), OK4.5 (COL), S3.2 (P1); also elsewhere on the board
+9V: C10.1, Q2.E, Q4.E, R1.2, R3.2, R5.2, R15.2, R17.2, R20.2, R35.2, R37.2, R38.2, R39.2, R41.2, R42.2, S3.1 (O1), S3.9 (S3), U1.P4, U2.3 (V+); also elsewhere on the board
AGND: S3.4 (O2); also elsewhere on the board
A_DIO2: JP7.2, LICK.P$SIG1 (SIG1); also elsewhere on the board
A_DIO4: JP8.2, LICK.P$SIG0 (SIG0); also elsewhere on the board
DGND: C4.2, C5.2, C8.2, C9.2, ISOLATED.K (C), LICK.P$GND0 (GND0), LICK.P$GND1 (GND1), R22.1, R25.1, R28.1, R34.1; also elsewhere on the board
GND-ISO: BAT1.-, C10.2, JP3.3, JP4.3, OK3.2 (C), OK4.2 (C), R16.E, R16.S, R21.E, R21.S, R36.1, R40.1, S3.5 (P2), U1.P1, U2.6 (-IN), U2.7 (+IN), U2.8 (-IN), U2.9 (+IN), U2.12 (GND); also elsewhere on the board
LICK_A0_IN: JP4.1, Q1.1 (G), R3.1, U1.P2
LICK_A0_OUT: C5.1, JP7.3, OK3.4 (EMI), R25.2
LICK_A1_IN: JP4.2, Q3.1 (G), R1.1, U1.P3
LICK_A1_OUT: C4.1, JP8.3, OK4.4 (EMI), R34.2
LICK_B0_IN: JP3.1, R38.1, U2.4 (-IN)
LICK_B0_OUT: C8.1, JP7.1, OK1.4 (EMI), R22.2
LICK_B1_IN: JP3.2, R42.1, U2.10 (-IN)
LICK_B1_OUT: C9.1, JP8.1, OK2.4 (EMI), R28.2
LICK_DETECT_A0: OK1.2 (C), R23.A, R35.1, U2.2 (OUT)
LICK_DETECT_A1: OK2.2 (C), R26.A, R39.1, U2.13 (OUT)
unnamed: Q1.3 (D), R17.1, R18.2
unnamed: Q3.3 (D), R5.1, R6.2
unnamed: Q4.B, R6.1
unnamed: OK4.1 (A), R8.2
unnamed: Q4.C, R8.1
unnamed: Q3.2 (S), R16.A
unnamed: Q2.B, R18.1
unnamed: OK3.1 (A), R19.2
unnamed: Q2.C, R19.1
unnamed: Q1.2 (S), R21.A
unnamed: BAT1.+, S3.8 (P3)
unnamed: ISOLATED.A, R43.1
unnamed: OK2.1 (A), R20.1
unnamed: R43.2, S3.3 (S1)
unnamed: OK1.1 (A), R15.1
unnamed: R23.E, R23.S, R36.2, R37.1, U2.5 (+IN)
unnamed: R26.E, R26.S, R40.2, R41.1, U2.11 (+IN)

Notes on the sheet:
ESD Protection for transistor gates

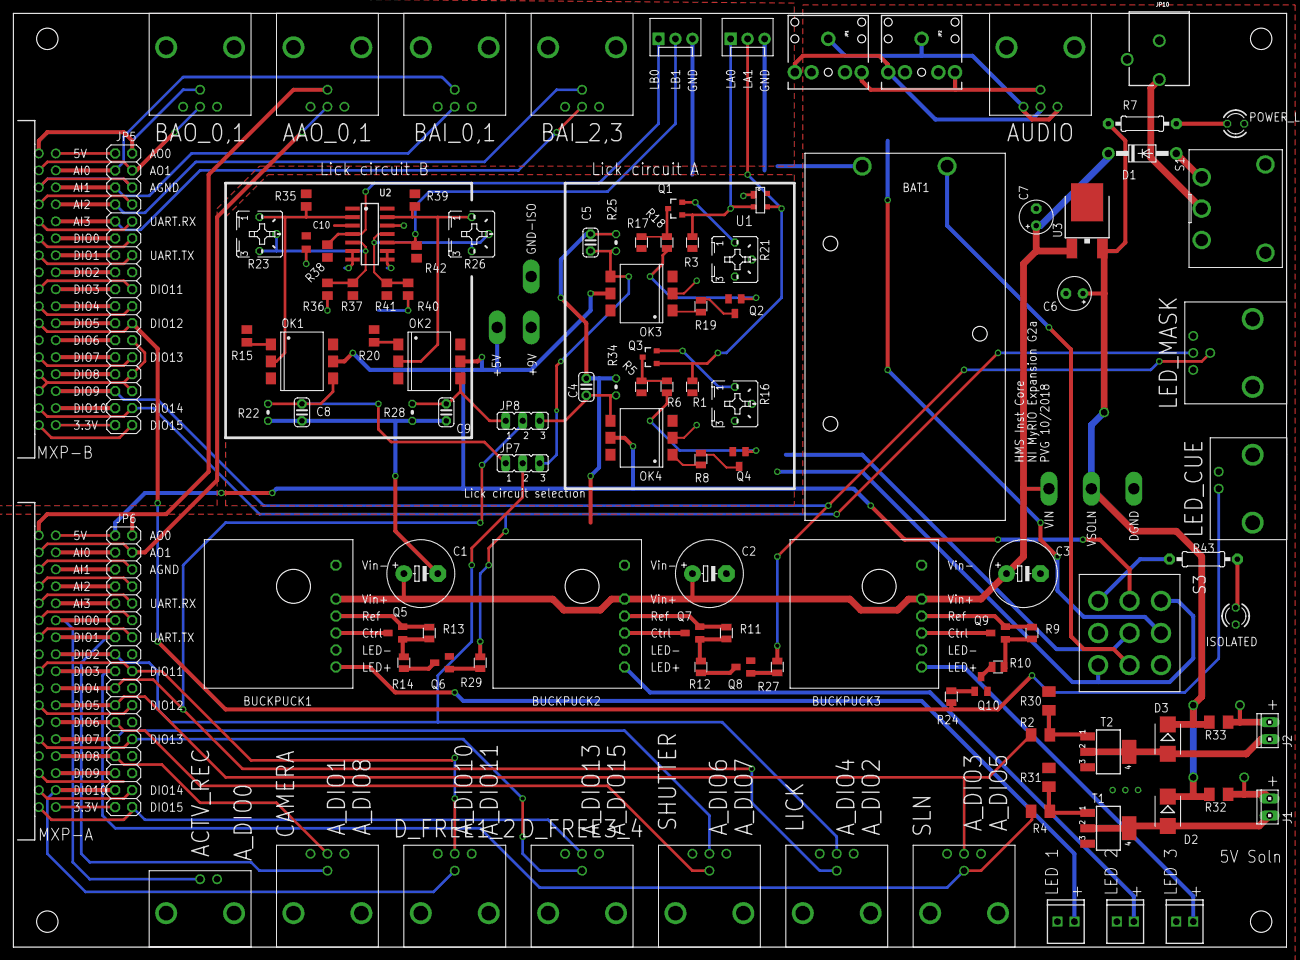
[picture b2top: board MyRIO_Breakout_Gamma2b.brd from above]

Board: 2 copper layers, 190.5 x 139.7 mm, 119 parts (0 on the bottom side), 116 nets.

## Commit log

2018-11-27 Create test

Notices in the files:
parts and their libraries:
SparkFun-Connectors: Licensing: Creative Commons ShareAlike 4.0 International - https://creativecommons.org/licenses/by-sa/4.0
op-amp: Copyright (C) 2015, Bob Starr
